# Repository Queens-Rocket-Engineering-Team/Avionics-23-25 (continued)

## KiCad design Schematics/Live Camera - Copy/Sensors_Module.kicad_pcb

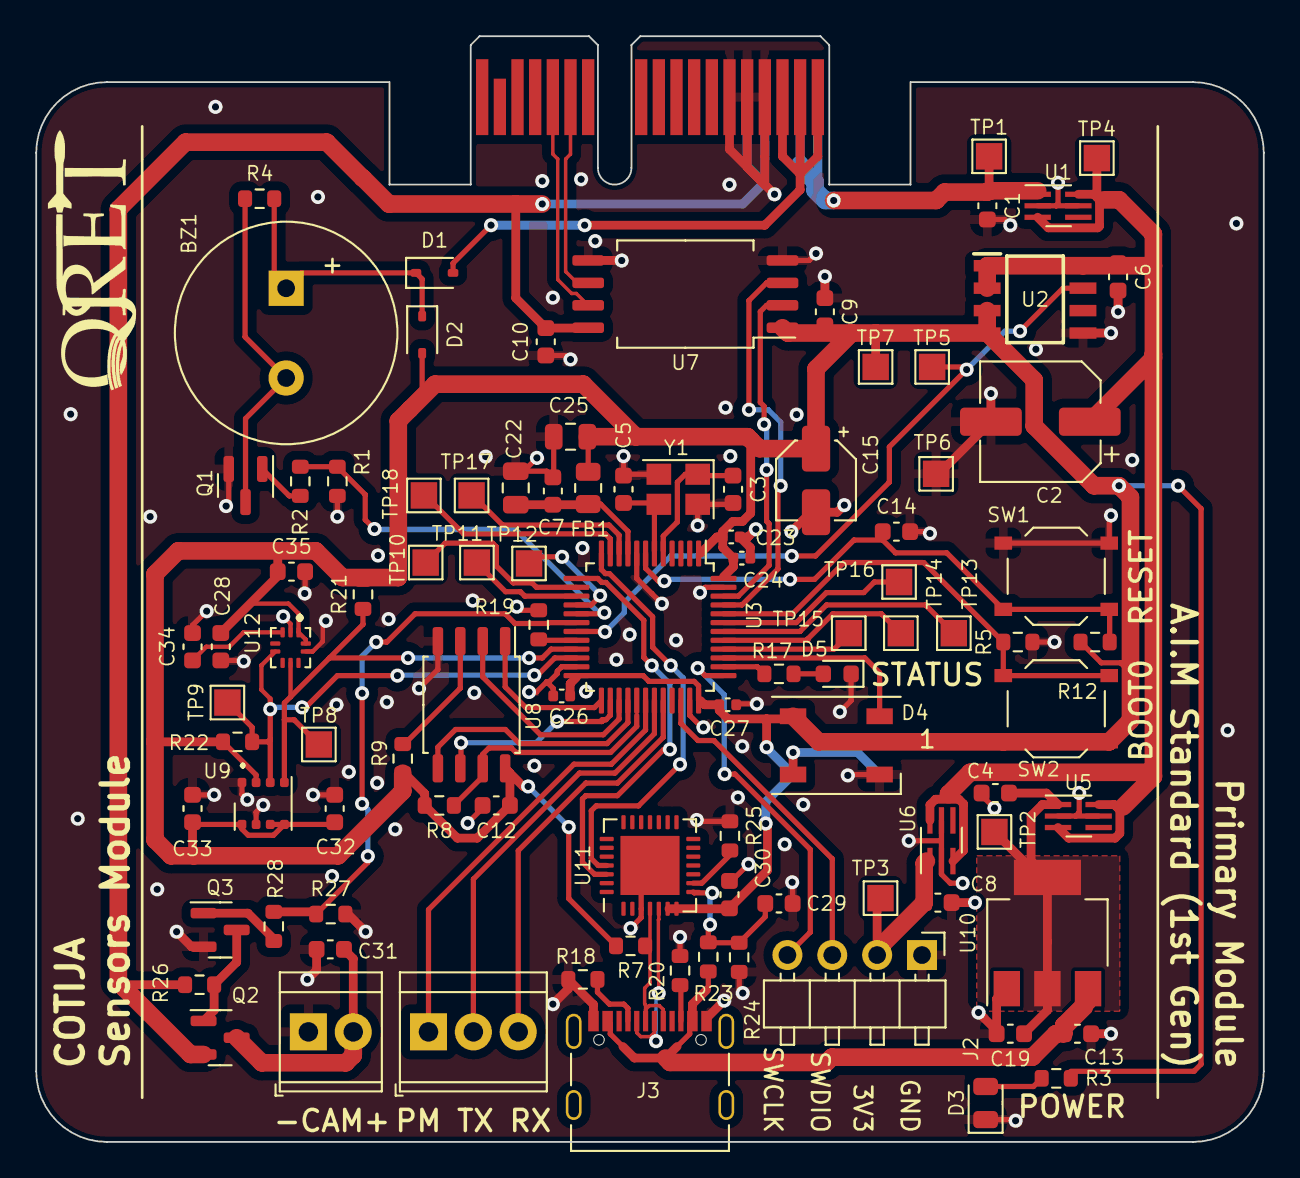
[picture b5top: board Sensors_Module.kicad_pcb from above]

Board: 2 copper layers, 69.5 x 62.6 mm, 98 parts (1 on the bottom side), 64 nets.

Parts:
BZ1: PKM13EPYH4000; Buzzer_12.6x9.5RM5.0
C1, C4, C8, C28, C29, C34, C35: 1uF; C_0603_1608Metric
C2: 100uF; CP_Elec_6.3x5.9
C3, C5: 10p; C_0603_1608Metric
C6: 0.1uF; C_0603_1608Metric
C7: 10n; C_0603_1608Metric
C9, C10: 0.1u; C_0603_1608Metric
C12, C14, C32, C33: 100nF; C_0603_1608Metric
C13, C19, C30, C31: 10uF; C_0603_1608Metric
C15: 10uF; CP_Elec_4x5.4
C22, C25: 1uF; C_0805_2012Metric
C23, C24, C26, C27: 100n; C_0402_1005Metric
D1, D2: 1N5819WS; D_SOD-323
D3: PWR_LED (GRN); LED_0805_2012Metric
D4, D6: WS2812B; LED_WS2812B_PLCC4_5.0x5.0mm_P3.2mm
D5: DB_LED (YLW); LED_0603_1608Metric
FB1: 100R; R_0805_2012Metric
J1: Stack Male Edge Connector; BUS_PCIexpress_x1
J2: SWD_01x04_Pin; SWD_PinHeader_1x04_P2.54mm_Horizontal
J3: USB_C_Female_USB2_Small; USB_C_DB-108PWB
J6: CAM_PWR; TerminalBlock_TE_282834-2_1x02_P2.54mm_Horizontal
J7: CAM_DAT; TerminalBlock_TE_282834-3_1x03_P2.54mm_Horizontal
Q1, Q3: AO3400A; SOT-23
Q2: AO3401A; SOT-23
R1, R8, R9, R12: 10k; R_0603_1608Metric
R2: 510R; R_0603_1608Metric
R3: 3.3k; R_0603_1608Metric
R4, R25: 1k; R_0603_1608Metric
R5, R19, R26, R27: 100k; R_0603_1608Metric
R7: 1.5k; R_0603_1608Metric
R17: 680R; R_0603_1608Metric
R18, R20: 5.1k; R_0603_1608Metric
R21, R22: 4.7k; R_0603_1608Metric
R23: 22k; R_0603_1608Metric
R24: 47k; R_0603_1608Metric
R28: 510; R_0603_1608Metric
SW1: SW_STM_RESET; SW_Push_1P1T_XKB_TS-1187A
SW2: SW_STM_BOOT_MODE; SW_Push_1P1T_XKB_TS-1187A
TP1: TP_VSTACK; TestPoint_Pad_1.5x1.5mm
TP2: TP_VUSB; TestPoint_Pad_1.5x1.5mm
TP3: TP_VSWD; TestPoint_Pad_1.5x1.5mm
TP4: TP_MUX; TestPoint_Pad_1.5x1.5mm
TP5: TP_ISENSE; TestPoint_Pad_1.5x1.5mm
TP6: TP_GND; TestPoint_Pad_1.5x1.5mm
TP7: TP_3V3; TestPoint_Pad_1.5x1.5mm
TP8: TP_SCL; TestPoint_Pad_1.5x1.5mm
TP9: TP_SDA; TestPoint_Pad_1.5x1.5mm
TP10: PA4; TestPoint_Pad_1.5x1.5mm
TP11: PA5; TestPoint_Pad_1.5x1.5mm
TP12: PA6; TestPoint_Pad_1.5x1.5mm
TP13: PB6; TestPoint_Pad_1.5x1.5mm
TP14: PB5; TestPoint_Pad_1.5x1.5mm
TP15: PB4; TestPoint_Pad_1.5x1.5mm
TP16: PB7; TestPoint_Pad_1.5x1.5mm
TP17: PA0; TestPoint_Pad_1.5x1.5mm
TP18: PA1; TestPoint_Pad_1.5x1.5mm
U1, U5, U6: LM66100DCKR; SC-70-6_Handsoldering
U2: ACS70331EOLC; SOIC127P600X175-8N
U3: STM32F103CBT6; LQFP-48_7x7mm_P0.5mm
U7: ISO1042BDWVR; SOIC-8 ISO1042BDWV
U8: W25Q128JVS; SOIC-8_5.23x5.23mm_P1.27mm
U9: BME680; Bosch_LGA-8_3x3mm_P0.8mm_ClockwisePinNumbering
U10: AMS1117-3.3; SOT-223-3_TabPin2
U11: CP2102N-Axx-xQFN28; QFN-28-1EP_5x5mm_P0.5mm_EP3.35x3.35mm
U12: BM1422AGMV; Rohm_MLGA010V020A_LGA-10_2x2mm_P0.45mm_LayoutBorder_3x2y
Y1: X322516MMB4SI; Crystal_SMD_3225-4Pin_3.2x2.5mm

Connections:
5V_RAW: C13.1, J3.A4 (VBUS), J3.A9 (VBUS), J3.B4 (VBUS), J3.B9 (VBUS), R23.2, U10.3 (VI)
+3.3V: C9.2, C12.1, C15.1, C23.1, C24.1, C25.1, C26.1, C27.1, C28.1, C30.2, C32.1, C33.1, C35.1, D2.2 (A), D4.1 (VDD), D6.1 (VDD), FB1.2, R3.2, R7.1, R8.2, R9.2, R12.2, R21.1, R22.2, SW2.2, TP7.1, U2.3 (IP-), U2.4 (IP-), U3.1 (VBAT), U3.24 (VDD), U3.36 (VDD), U3.48 (VDD), U7.1 (VCC1), U8.8 (VCC), U9.2 (CSB), U9.5 (SDO), U9.6 (VDDIO), U9.8 (VDD), U11.6 (VDD), U11.7 (VREGIN), U12.1 (AVDD), U12.10 (DVDD)
+3.3VA: C7.1, C22.1, FB1.1, U3.9 (VDDA)
+5V: C10.2, J1.A4 (5.0V_A), J1.A5 (5.0V_A), Q2.2 (S), R26.1, U7.8 (VCC2)
+BATT: D1.2 (A), J1.B1 (BATT_A), J1.B2 (BATT_A), J1.B3 (BATT_A)
BOOT0: R5.2, SW2.1, U3.44 (BOOT0)
BOOT1: R19.2, U3.20 (PB2)
BUZZER: R1.2, R2.2, U3.17 (PA7)
CAM_5V: C31.1, J6.2, Q2.3 (D)
CAM_PWM: J7.3, U3.32 (PA11)
CAM_PWR: R27.1, R28.1, U3.18 (PB0)
CAM_RX: J7.2, U3.31 (PA10)
CAM_TX: J7.1, U3.30 (PA9)
CAN_H: J1.B14 (CAN_H), U7.7 (CANH)
CAN_L: J1.B13 (CAN_L), U7.6 (CANL)
CAN_RX: U3.45 (PB8), U7.3 (RXD)
CAN_TX: U3.46 (PB9), U7.2 (TXD)
CS_FL: U3.25 (PB12), U8.1 (~CS)
CURR_SENSE: TP5.1, U2.7 (VOUT), U3.19 (PB1)
DB_LED: R17.2, U3.38 (PA15)
GND: C1.2, C2.2, C3.2, C4.2, C5.2, C6.2, C7.2, C8.2, C9.1, C10.1, C12.2, C13.2, C14.2, C15.2, C19.2, C22.2, C23.2, C24.2, C25.2, C26.2, C27.2, C28.2, C29.1, C30.1, C31.2, C32.2, C33.2, C34.2, C35.2, D3.1 (K), D4.3 (VSS), D5.1 (K), D6.3 (VSS), J1.A3 (GND_A), J1.A6 (GND_A), J1.B4 (GND_A), J1.B5 (GND_A), J1.B6 (GND_A), J2.1 (GND), J3.A1 (GND), J3.A12 (GND), J3.B1 (GND), J3.B12 (GND), J6.1, Q1.2 (S), Q3.2 (S), R1.1, R5.1, R18.2, R19.1, R20.2, R24.1, R25.2, R27.2, SW1.1, TP6.1, U1.2 (GND), U1.5 (ST), U2.5 (GND), U3.8 (VSSA), U3.23 (VSS), U3.35 (VSS), U3.47 (VSS), U5.2 (GND), U5.5 (ST), U6.2 (GND), U6.5 (ST), U7.4 (GND1), U7.5 (GND2), U8.4 (GND), U9.1 (GND), U9.7 (GND), U10.1 (GND), U11.3 (GND), U11.29 (GND), U12.2 (GND), U12.9 (ADDR), Y1.2, Y1.4
MISO_FL: U3.27 (PB14), U8.2 (DO(IO1))
MOSI_FL: U3.28 (PB15), U8.5 (DI(IO0))
unnamed: BZ1.2 (+), Q1.3 (D), R4.1
unnamed: BZ1.1 (-), D1.1 (K), D2.1 (K), R4.2
unnamed: D3.2 (A), R3.1
unnamed: D4.2 (DOUT), D6.4 (DIN)
unnamed: D5.2 (A), R17.1
unnamed: J3.A5 (CC1), R18.1
unnamed: J3.B5 (CC2), R20.1
unnamed: Q1.1 (G), R2.1
unnamed: Q2.1 (G), Q3.3 (D), R26.2
unnamed: Q3.1 (G), R28.2
unnamed: TP17.1, U3.10 (PA0)
unnamed: TP18.1, U3.11 (PA1)
unnamed: TP10.1, U3.14 (PA4)
unnamed: TP11.1, U3.15 (PA5)
unnamed: TP12.1, U3.16 (PA6)
unnamed: TP15.1, U3.40 (PB4)
unnamed: TP14.1, U3.41 (PB5)
unnamed: TP13.1, U3.42 (PB6)
unnamed: TP16.1, U3.43 (PB7)
unnamed: R9.1, U8.3 (IO2)
unnamed: C29.2, R23.1, R24.2, U11.8 (VBUS)
unnamed: R25.1, U11.9 (~RST)
unnamed: C34.1, U12.3 (VREG)
OSC_IN: C3.1, U3.5 (PD0), Y1.1
OSC_OUT: C5.1, U3.6 (PD1), Y1.3
RESET_FL: R8.1, U3.29 (PA8), U8.7 (IO3)
RGB_DATA: D4.4 (DIN), U3.39 (PB3)
SCK_FL: U3.26 (PB13), U8.6 (CLK)
SCL: R21.2, TP8.1, U3.21 (PB10), U9.4 (SCK), U12.7 (SCL)
SDA: R22.1, TP9.1, U3.22 (PB11), U9.3 (SDI), U12.5 (SDA)
STM_RESET: C14.1, R12.1, SW1.2, U3.7 (NRST)
SWCLK: J2.4 (SWCLK), U3.37 (PA14)
SWDIO: J2.3 (SWDIO), U3.34 (PA13)
USB_D+: J3.A6 (D+), J3.B6 (D+), R7.2, U11.4 (D+)
USB_D-: J3.A7 (D-), J3.B7 (D-), U11.5 (D-)
USB_RX: U3.13 (PA3), U11.26 (TXD)
USB_TX: U3.12 (PA2), U11.25 (RXD)
V_MUX: C2.1, C6.1, TP4.1, U1.3 (*CE), U1.6 (VOUT), U2.1 (IP+), U2.2 (IP+), U2.8 (VCC), U5.3 (*CE), U5.6 (VOUT), U6.3 (*CE), U6.6 (VOUT)
V_PSU: C1.1, J1.A1 (3.3V_A), J1.A2 (3.3V_A), TP1.1, U1.1 (VIN)
V_REGUSB: C4.1, C19.1, TP2.1, U5.1 (VIN), U10.2 (VO)
V_SWD: C8.1, J2.2 (3V3), TP3.1, U6.1 (VIN)

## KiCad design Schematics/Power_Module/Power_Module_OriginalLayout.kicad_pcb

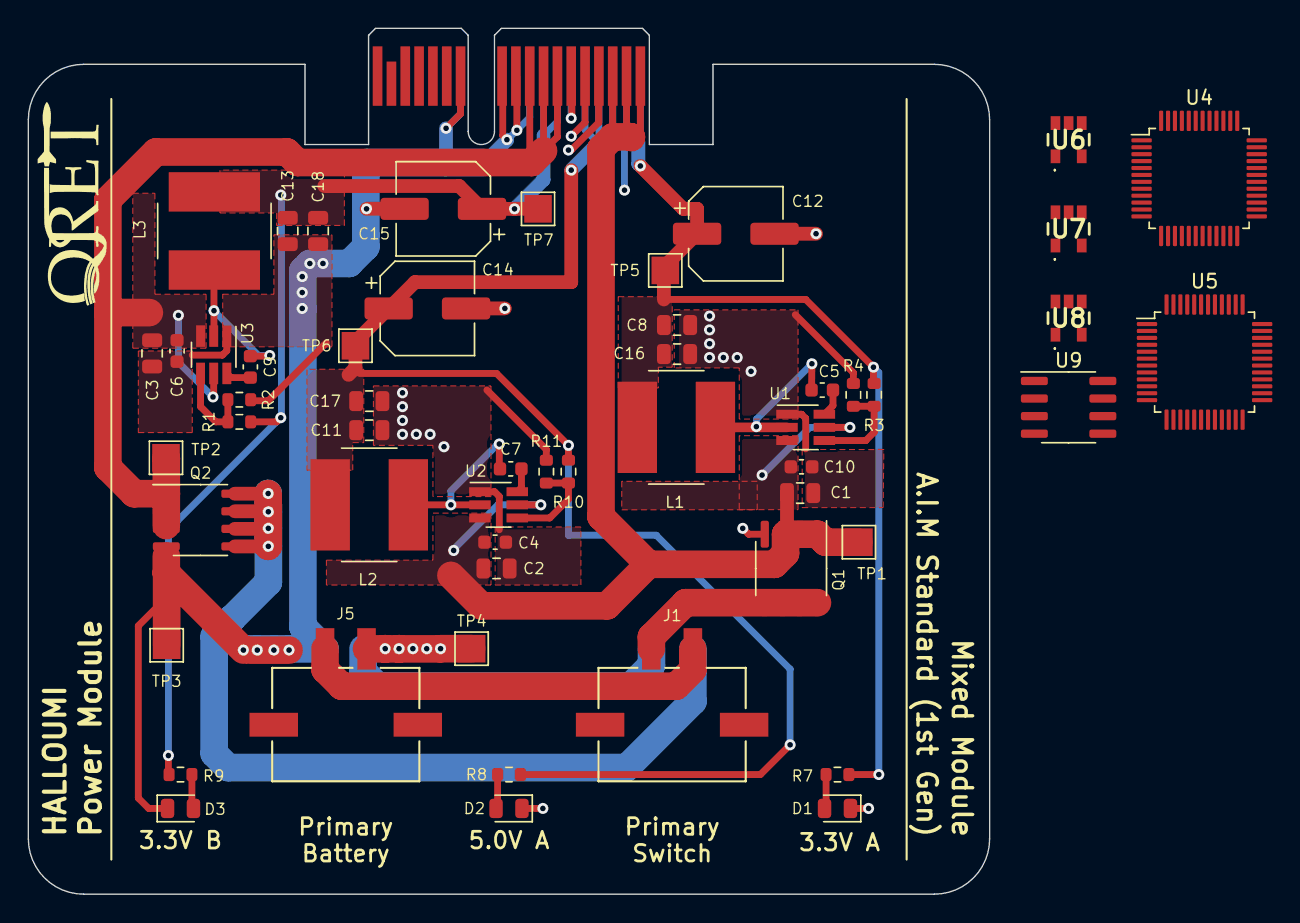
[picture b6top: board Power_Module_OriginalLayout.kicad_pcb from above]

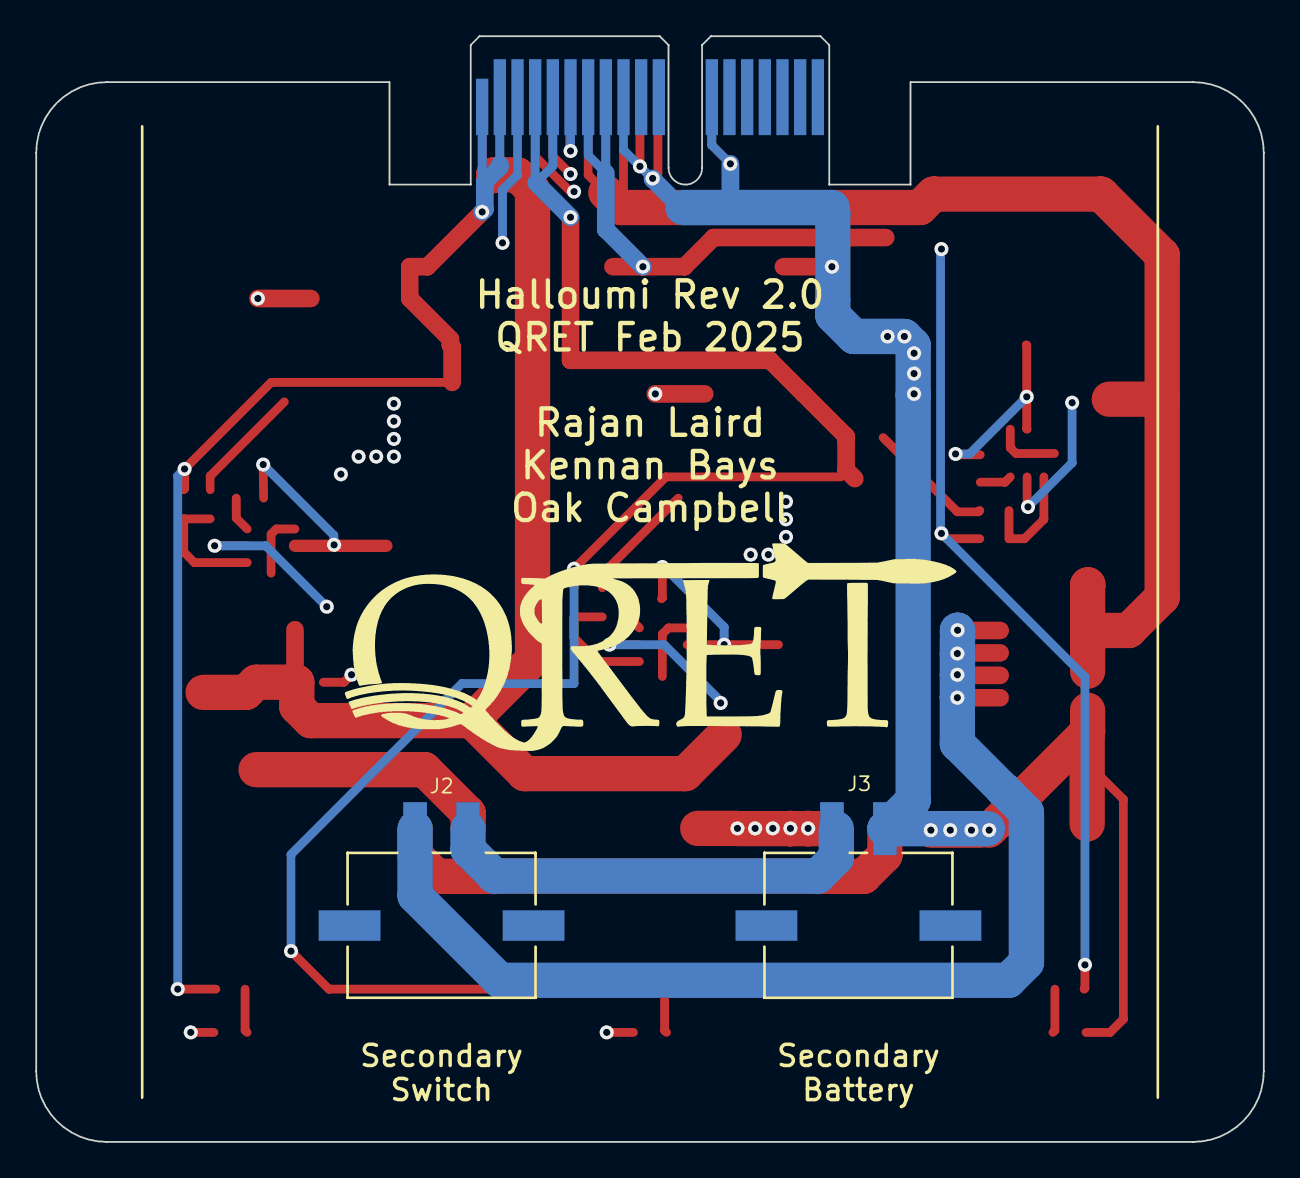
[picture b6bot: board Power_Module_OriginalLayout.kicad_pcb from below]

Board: 4 copper layers, 69.5 x 62.6 mm, 56 parts (2 on the bottom side), 25 nets.

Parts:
C1, C2, C3: 4.7uF; C_0805_2012Metric
C4, C5, C6, C7, C9, C10: 100nF; C_0603_1608Metric
C8, C11, C13, C16, C17, C18: 22uF; C_0805_2012Metric
C12, C14, C15: 100uF; CP_Elec_6.3x5.9
D1: 3.3V_A PWR (GRN); LED_0805_2012Metric
D2: 5.0V_A PWR (RED); LED_0805_2012Metric
D3: 3.3V_B PWR (GRN); LED_0805_2012Metric
J1: ScrewSwitch A; CONN_2-1445057-2_TYCO
J2: ScrewSwitch B; CONN_2-1445057-2_TYCO
J3: Battery B; CONN_2-1445057-2_TYCO
J5: Battery A; CONN_2-1445057-2_TYCO
J6: Stack Male Edge Connector; BUS_PCIexpress_x1
L1, L3: 5.6uH; L_Bourns_SRN8040TA
L2: 6.8uH; L_Bourns_SRN8040TA
Q1, Q2: AO4447A; SOIC-8_3.9x4.9mm_P1.27mm
R1, R3: 100k; R_0603_1608Metric
R2, R4: 22k; R_0603_1608Metric
R7, R9: 1.2k; R_0603_1608Metric
R8: 2.4k; R_0603_1608Metric
R10: 56k; R_0603_1608Metric
R11: 7.5k; R_0603_1608Metric
TP1: TP_BATT1; TestPoint_Pad_2.0x2.0mm
TP2: TP_BATT2; TestPoint_Pad_2.0x2.0mm
TP3: TP_GND2; TestPoint_Pad_2.0x2.0mm
TP4: TP_GND1; TestPoint_Pad_2.0x2.0mm
TP5: TP_3.3V_A; TestPoint_Pad_2.0x2.0mm
TP6: TP_5.0V_A; TestPoint_Pad_2.0x2.0mm
TP7: TP_3.3V_B; TestPoint_Pad_2.0x2.0mm
U1, U2, U3: LMR51430XDDCR; SOT-23-6_Handsoldering
U4, U5: STM32F103C8Tx; LQFP-48_7x7mm_P0.5mm
U6, U7, U8: ACS37041KLHBLT-010B3; APS12628LLHALTBAP
U9: ISO6421 OR SMTHN; SOIC-8_3.9x4.9mm_P1.27mm

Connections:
3.3V_A: C8.1, C12.1, C16.1, J6.A1 (3.3V_A), J6.A2 (3.3V_A), L1.2, R3.1, R7.1, TP5.1
3.3V_B: C13.1, C15.1, C18.1, J6.A7 (3.3V_B), J6.A8 (3.3V_B), L3.2, R1.1, R9.1, TP7.1
5.0V_A: C11.1, C14.1, C17.1, J6.A4 (5.0V_A), J6.A5 (5.0V_A), L2.2, R8.1, R10.1, TP6.1
BATT_A: C1.1, C2.1, C4.1, C10.1, J6.B1 (BATT_A), J6.B2 (BATT_A), J6.B3 (BATT_A), Q1.1 (S), Q1.2 (S), Q1.3 (S), TP1.1, U1.3 (VIN), U1.5 (EN), U2.3 (VIN), U2.5 (EN)
BATT_B: C3.1, C6.1, J6.B7 (BATT_B), J6.B8 (BATT_B), J6.B9 (BATT_B), Q2.1 (S), Q2.2 (S), Q2.3 (S), TP2.1, U3.3 (VIN), U3.5 (EN)
GND: C1.2, C2.2, C4.2, C8.2, C10.2, C11.2, C12.2, C14.2, C16.2, C17.2, D1.1 (K), D2.1 (K), J5.1, J6.A3 (GND_A), J6.A6 (GND_A), J6.B4 (GND_A), J6.B5 (GND_A), J6.B6 (GND_A), Q1.4 (G), R4.2, R11.2, TP4.1, U1.1 (GND), U2.1 (GND)
GND2: C3.2, C6.2, C13.2, C15.2, C18.2, D3.1 (K), J3.1, J6.A9 (GND_B), J6.A12 (GND_B), J6.B10 (GND_B), J6.B11 (GND_B), J6.B12 (GND_B), Q2.4 (G), R2.2, TP3.1, U3.1 (GND)
unnamed: D1.2 (A), R7.2
unnamed: D2.2 (A), R8.2
unnamed: D3.2 (A), R9.2
unnamed: J1.1, J5.2
unnamed: J1.2, Q1.5 (D), Q1.6 (D), Q1.7 (D), Q1.8 (D)
unnamed: J2.1, J3.2
unnamed: J2.2, Q2.5 (D), Q2.6 (D), Q2.7 (D), Q2.8 (D)
unnamed: C5.2, U1.6 (CB)
unnamed: R3.2, R4.1, U1.4 (FB)
unnamed: C5.1, L1.1, U1.2 (SW)
unnamed: C7.2, U2.6 (CB)
unnamed: R10.2, R11.1, U2.4 (FB)
unnamed: C7.1, L2.1, U2.2 (SW)
unnamed: C9.2, U3.6 (CB)
unnamed: R1.2, R2.1, U3.4 (FB)
unnamed: C9.1, L3.1, U3.2 (SW)
unnamed: U4.23 (VSS), U4.35 (VSS), U4.47 (VSS)
unnamed: U5.23 (VSS), U5.35 (VSS), U5.47 (VSS)
